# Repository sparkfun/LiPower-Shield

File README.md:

**NOTE:** *This product has been retired from our catalog. If you are looking for more up-to-date info, please check out some of these resources to see how other users are still hacking and improving on this product.*
* *[SparkFun Forum](https://forum.sparkfun.com/)*
* *[Comments Here on GitHub](https://github.com/sparkfun/LiPower-Shield/issues)*
* *[IRC Channel](https://www.sparkfun.com/news/263)*

SparkFun LiPower Shield
========================

[*SparkFun LiPower Shield (DEV-13158)*](https://www.sparkfun.com/products/13158)

This shield allows your Arduino to be powered from a 3.7V LiPo battery, while also charge and monitor the battery. 

Repository Contents
-------------------

* **/Hardware** - All Eagle design files (.brd, .sch)
* **/Production** - Production panel files (.brd)

Product Versions
----------------

* [DEV-13158](https://www.sparkfun.com/products/13158)- Version 1.1. Retired.
* [DEV-10711](https://www.sparkfun.com/products/retired/10711)- Version 1. Retired.

GitHub Version History
---------------
* [Version 1.1](https://github.com/sparkfun/LiPower-Shield/tree/V_1.1) - Latest hardware files. Retired..
* [Version 1](https://github.com/sparkfun/LiPower-Shield/tree/V_1) - Version 1. Retired. 

License Information
-------------------

This product is _**open source**_! 

Please review the LICENSE.md file for license information. 

If you have any questions or concerns on licensing, please contact techsupport@sparkfun.com.

Distributed as-is; no warranty is given.

- Your friends at SparkFun.

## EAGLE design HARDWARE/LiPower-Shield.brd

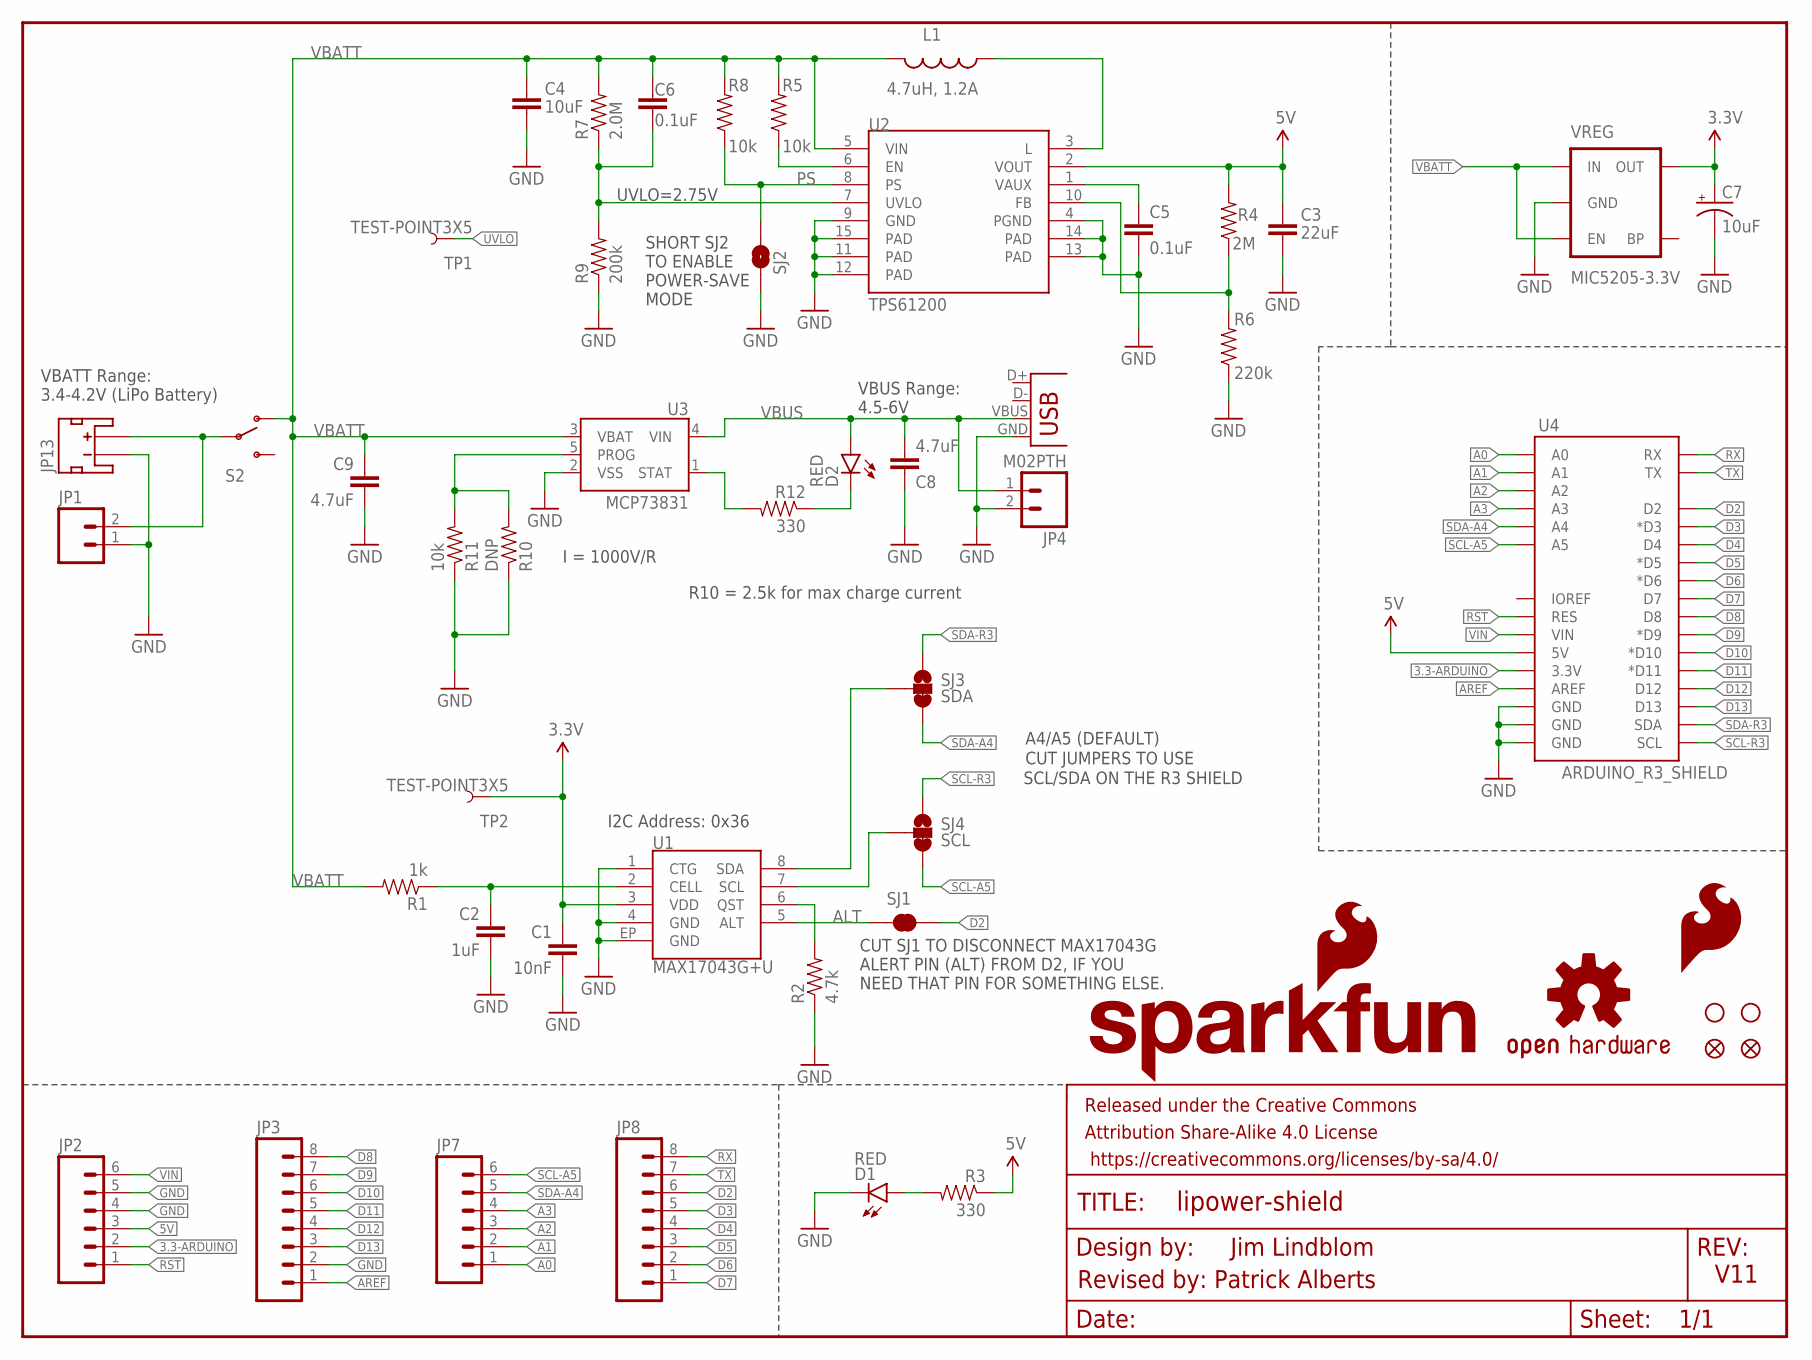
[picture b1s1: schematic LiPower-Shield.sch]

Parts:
C1: 10nF; 0603-CAP
C2: 1uF; 0603-CAP
C3: 22uF; 0805
C4: 10uF; 1206
C5, C6: 0.1uF; 0603-CAP
C7: 10uF; EIA3216
C8, C9: 4.7uF; 0603-CAP
D1, D2: RED; LED-0603
FID1, FID2: FIDUCIAL1X2; FIDUCIAL-1X2
FRAME1: FRAME-LETTER; CREATIVE_COMMONS
JP1: M021X02_NO_SILK; 1X02_NO_SILK
JP2, JP7: M06NO_SILK; 1X06_NO_SILK
JP3, JP8: M08NO_SILK; 1X08_NO_SILK
JP4: M02PTH; 1X02
JP9, JP10: STAND-OFFTIGHT; STAND-OFF-TIGHT
JP11: USBSMD; USB-MINIB
JP13: JST_2MM_MALE; JST-2-SMD
L1: 4.7uH, 1.2A; INDUCTOR_4.7UH
LOGO1: OSHW-LOGOS; OSHW-LOGO-S
LOGO2: SFE_LOGO_NAME_FLAME.2_INCH; SFE_LOGO_NAME_FLAME_.2
LOGO3: SFE_LOGO_FLAME.1_INCH; SFE_LOGO_FLAME_.1
R1: 1k; 0603-RES
R2: 4.7k; 0603-RES
R3, R12: 330; 0603-RES
R4: 2M; 0603-RES
R5, R8, R11: 10k; 0603-RES
R6: 220k; 0603-RES
R7: 2.0M; 0603-RES
R9: 200k; 0603-RES
R10: DNP; 1/6W-RES
S2: SWITCH-SPDT-SMD-A; SWITCH-SPST-SMD-A
SJ1: SOLDERJUMPERTRACE; SJ_2S-TRACE
SJ2: PS; SJ_2S-NO
SJ3: SDA; PAD-JUMPER-3-2OF3_NC_BY_TRACE_YES_SILK_FULL_BOX
SJ4: SCL; PAD-JUMPER-3-2OF3_NC_BY_TRACE_YES_SILK_FULL_BOX
TP1, TP2: TEST-POINT3X5; PAD.03X.05
U1: MAX17043G+U; TDFN-8
U2: TPS61200; QFN-10_PAD
U3: MCP73831; SOT23-5
U4: ARDUINO_R3_SHIELD; UNO_R3_SHIELD
VREG: MIC5205-3.3V; SOT23-5

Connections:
3.3-ARDUINO: JP2.2, U4.3.3V
3.3V: C1.1, C7.A (+), TP2.P$1, U1.3 (VDD), VREG.5 (OUT)
5V: C3.1, JP2.3, R3.1, R4.2, U2.2 (VOUT), U4.5V
A0: JP7.1, U4.A0
A1: JP7.2, U4.A1
A2: JP7.3, U4.A2
A3: JP7.4, U4.A3
ALT: SJ1.1, U1.5 (ALT)
AREF: JP3.1, U4.AREF
CELL: C2.1, R1.1, U1.2 (CELL)
D2: JP8.6, SJ1.2, U4.D2
D3: JP8.5, U4.D3 (*D3)
D4: JP8.4, U4.D4
D5: JP8.3, U4.D5 (*D5)
D6: JP8.2, U4.D6 (*D6)
D7: JP8.1, U4.D7
D8: JP3.8, U4.D8
D9: JP3.7, U4.D9 (*D9)
D10: JP3.6, U4.D10 (*D10)
D11: JP3.5, U4.D11 (*D11)
D12: JP3.4, U4.D12
D13: JP3.3, U4.D13
EN: R5.1, U2.6 (EN)
FB: R4.1, R6.2, U2.10 (FB)
GND: C1.2, C2.2, C3.2, C4.2, C5.2, C7.C (-), C8.1, C9.2, D1.C, JP1.1, JP2.4, JP2.5, JP3.2, JP4.2, JP11.GND, JP13.1 (-), R2.1, R6.1, R9.1, R10.1, R11.1, SJ2.1, U1.1 (CTG), U1.4 (GND), U1.EP (GND), U2.4 (PGND), U2.9 (GND), U2.11 (PAD), U2.12 (PAD), U2.13 (PAD), U2.14 (PAD), U2.15 (PAD), U3.2 (VSS), U4.GND@0 (GND), U4.GND@1 (GND), U4.GND@2 (GND), VREG.2 (GND)
unnamed: D1.A, R3.2
unnamed: L1.P$1 (1), U2.3 (L)
unnamed: C5.1, U2.1 (VAUX)
unnamed: D2.C, R12.1
unnamed: JP1.2, JP13.2 (+), S2.2
unnamed: SJ3.2, U1.8 (SDA)
PROG: R10.2, R11.2, U3.5 (PROG)
PS: R8.1, SJ2.2, U2.8 (PS)
QST: R2.2, U1.6 (QST)
RST: JP2.1, U4.RES
RX: JP8.8, U4.RX
SCL: SJ4.2, U1.7 (SCL)
SCL-A5: JP7.6, SJ4.3, U4.A5
SCL-R3: SJ4.1, U4.SCL
SDA-A4: JP7.5, SJ3.3, U4.A4
SDA-R3: SJ3.1, U4.SDA
STAT: R12.2, U3.1 (STAT)
TX: JP8.7, U4.TX
UVLO: C6.2, R7.1, R9.2, TP1.P$1, U2.7 (UVLO)
VBATT: C4.1, C6.1, C9.1, L1.P$2 (2), R1.2, R5.2, R7.2, R8.2, S2.1 (O), U2.5 (VIN), U3.3 (VBAT), VREG.1 (IN), VREG.3 (EN)
VBUS: C8.2, D2.A, JP4.1, JP11.VBUS, U3.4 (VIN)
VIN: JP2.6, U4.VIN

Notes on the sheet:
I = 1000V/R
R10 = 2.5k for max charge current
UVLO=2.75V
V11
Jim Lindblom
Revised by: Patrick Alberts
A4/A5 (DEFAULT)
CUT JUMPERS TO USE
SCL/SDA ON THE R3 SHIELD
SHORT SJ2 TO ENABLE POWER-SAVE MODE
CUT SJ1 TO DISCONNECT MAX17043G ALERT PIN (ALT) FROM D2, IF YOU NEED THAT PIN FOR SOMETHING ELSE.
I2C Address: 0x36
VBATT Range: 3.4-4.2V (LiPo Battery)
VBUS Range: 4.5-6V

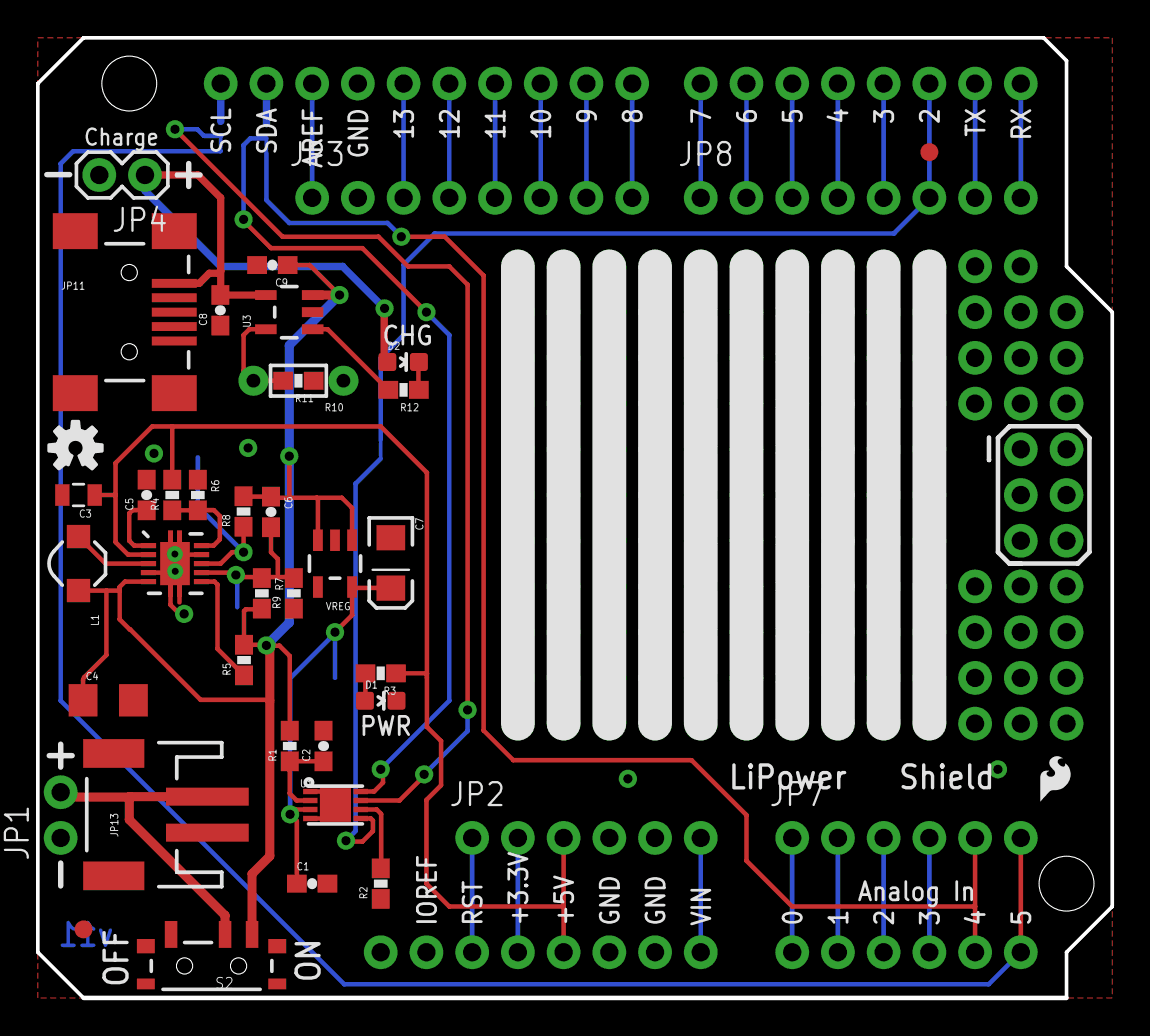
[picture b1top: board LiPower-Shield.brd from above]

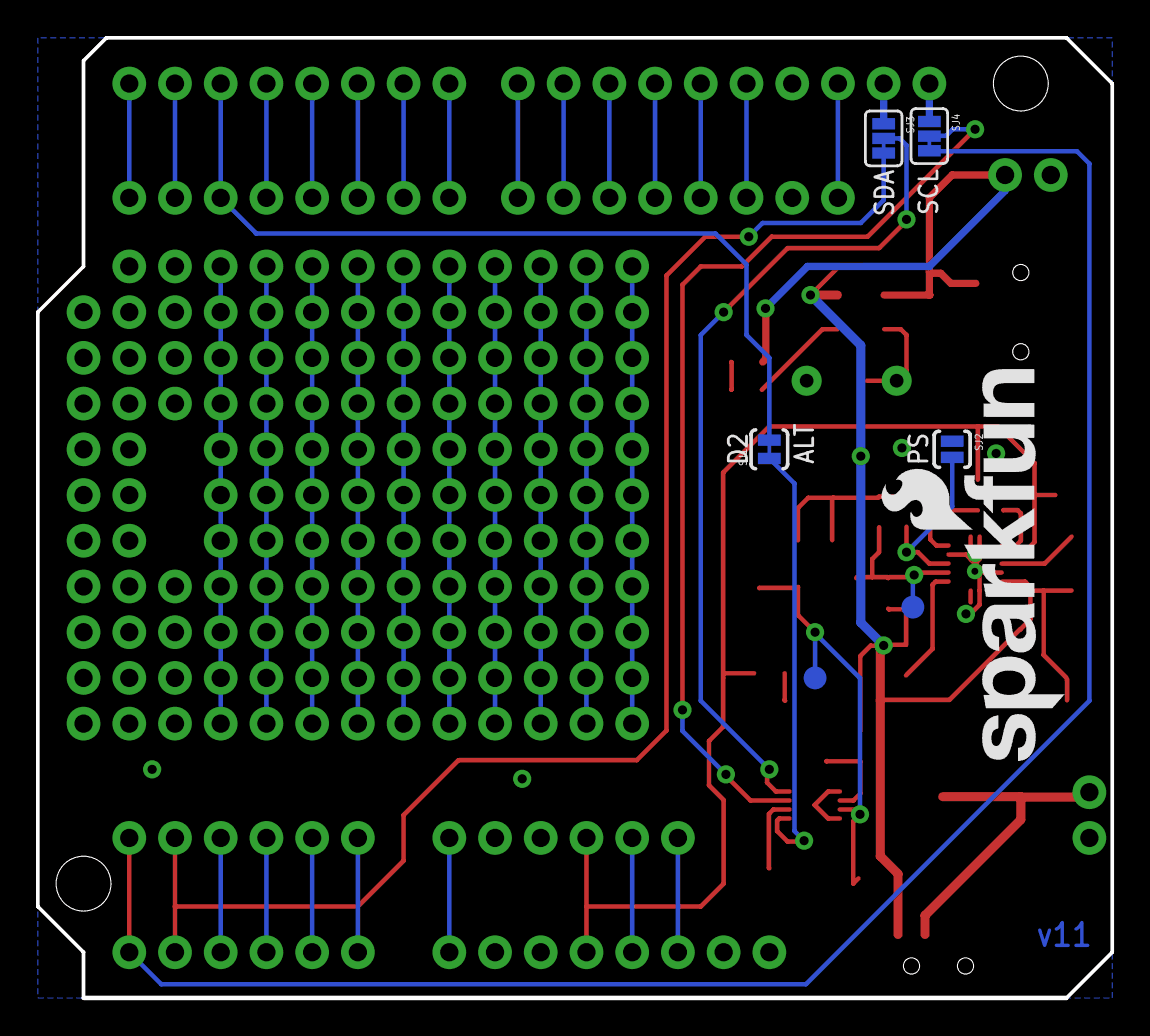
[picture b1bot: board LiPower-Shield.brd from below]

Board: 2 copper layers, 59.6 x 53.3 mm, 52 parts (7 on the bottom side), 47 nets.

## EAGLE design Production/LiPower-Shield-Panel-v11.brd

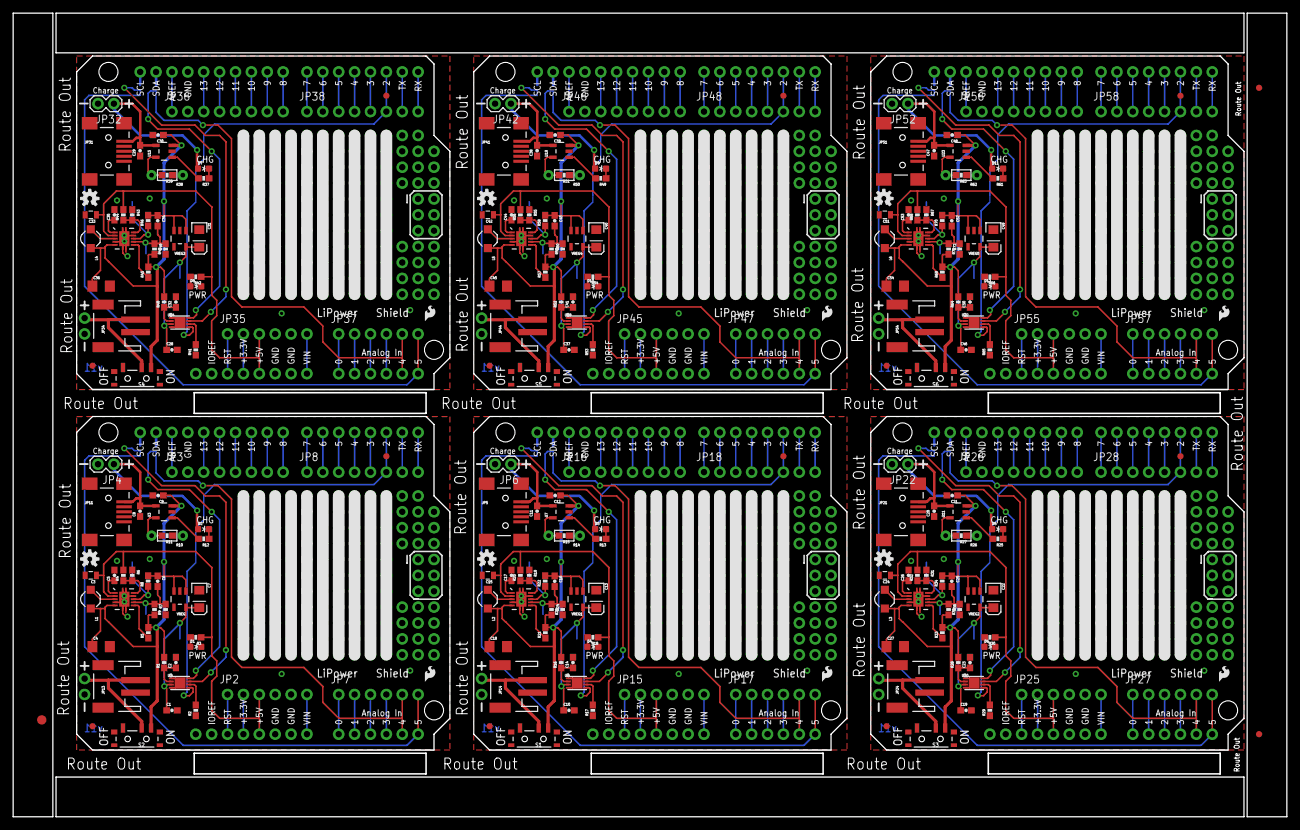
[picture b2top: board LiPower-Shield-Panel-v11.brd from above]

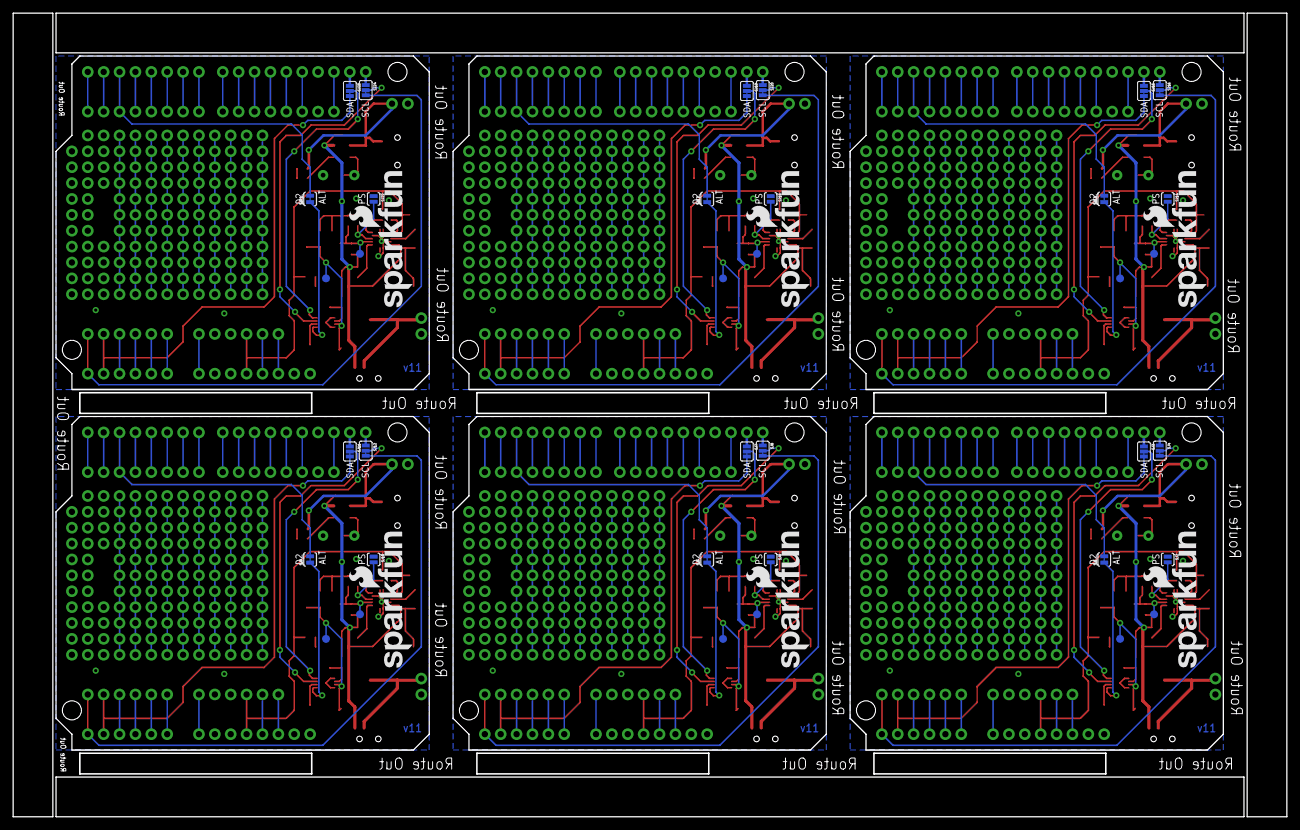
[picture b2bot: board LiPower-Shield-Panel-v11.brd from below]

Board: 2 copper layers, 203.7 x 128.5 mm, 309 parts (42 on the bottom side), 282 nets.

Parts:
C1, C10, C19, C28, C37, C46: 10nF; 0603-CAP
C2, C14, C23, C32, C41, C50: 1uF; 0603-CAP
C3, C15, C24, C33, C42, C51: 22uF; 0805
C4, C18, C27, C36, C45, C54: 10uF; 1206
C5, C6, C16, C17, C25, C26, C34, C35, C43, C44, C52, C53: 0.1uF; 0603-CAP
C7, C13, C22, C31, C40, C49: 10uF; EIA3216
C8, C9, C11, C12, C20, C21, C29, C30, C38, C39, C47, C48: 4.7uF; 0603-CAP
D1, D2, D3, D4, D5, D6, D7, D8, D9, D10, D11, D12: RED; LED-0603
E$1: FIDUCIAL-1.5X3
E$6, E$7: FIDUCIAL-1X2
FID1, FID2, FID3, FID4, FID5, FID6, FID7, FID8, FID9, FID10, FID11, FID12: FIDUCIAL1X2; FIDUCIAL-1X2
JP1, JP12, JP23, JP33, JP43, JP53: 1X02_NO_SILK
JP2, JP7, JP15, JP17, JP25, JP27, JP35, JP37, JP45, JP47, JP55, JP57: 1X06_NO_SILK
JP3, JP8, JP16, JP18, JP26, JP28, JP36, JP38, JP46, JP48, JP56, JP58: 1X08_NO_SILK
JP4, JP6, JP22, JP32, JP42, JP52: M02PTH; 1X02
JP5, JP11, JP21, JP31, JP41, JP51: USBSMD; USB-MINIB
JP9, JP10, JP19, JP20, JP29, JP30, JP39, JP40, JP49, JP50, JP59, JP60: STAND-OFFTIGHT; STAND-OFF-TIGHT
JP13, JP14, JP24, JP34, JP44, JP54: JST-2-SMD
L1, L2, L3, L4, L5, L6: 4.7uH, 1.2A; INDUCTOR_4.7UH
LOGO1, LOGO4, LOGO7, LOGO10, LOGO13, LOGO16: OSHW-LOGOS; OSHW-LOGO-S
LOGO2, LOGO5, LOGO8, LOGO11, LOGO14, LOGO17: SFE_LOGO_NAME_FLAME.2_INCH; SFE_LOGO_NAME_FLAME_.2
LOGO3, LOGO6, LOGO9, LOGO12, LOGO15, LOGO18: SFE_LOGO_FLAME.1_INCH; SFE_LOGO_FLAME_.1
R1, R16, R28, R40, R52, R64: 1k; 0603-RES
R2, R17, R29, R41, R53, R65: 4.7k; 0603-RES
R3, R12, R13, R18, R25, R30, R37, R42, R49, R54, R61, R66: 330; 0603-RES
R4, R20, R32, R44, R56, R68: 2M; 0603-RES
R5, R8, R11, R15, R21, R22, R27, R33, R34, R39, R45, R46, R51, R57, R58, R63, R69, R70: 10k; 0603-RES
R6, R19, R31, R43, R55, R67: 220k; 0603-RES
R7, R24, R36, R48, R60, R72: 2.0M; 0603-RES
R9, R23, R35, R47, R59, R71: 200k; 0603-RES
R10, R14, R26, R38, R50, R62: DNP; 1/6W-RES
S1, S2, S3, S4, S5, S6: SWITCH-SPST-SMD-A
SJ1, SJ5, SJ9, SJ13, SJ17, SJ21: SOLDERJUMPERTRACE; SJ_2S-TRACE
SJ2, SJ6, SJ10, SJ14, SJ18, SJ22: PS; SJ_2S-NO
SJ3, SJ7, SJ11, SJ15, SJ19, SJ23: SDA; PAD-JUMPER-3-2OF3_NC_BY_TRACE_YES_SILK_FULL_BOX
SJ4, SJ8, SJ12, SJ16, SJ20, SJ24: SCL; PAD-JUMPER-3-2OF3_NC_BY_TRACE_YES_SILK_FULL_BOX
TP1, TP2, TP3, TP4, TP5, TP6, TP7, TP8, TP9, TP10, TP11, TP12: TEST-POINT3X5; PAD.03X.05
U1, U6, U10, U14, U18, U22: MAX17043G+U; TDFN-8
U2, U8, U12, U16, U20, U24: TPS61200; QFN-10_PAD
U3, U7, U11, U15, U19, U23: MCP73831; SOT23-5
U4, U5, U9, U13, U17, U21: ARDUINO_R3_SHIELD; UNO_R3_SHIELD
VREG, VREG1, VREG2, VREG3, VREG4, VREG5: MIC5205-3.3V; SOT23-5

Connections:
3.3-ARDUINO: JP2.2, U4.3.3V
3.3-ARDUINO1: JP15.2, U5.3.3V
3.3-ARDUINO2: JP25.2, U9.3.3V
3.3-ARDUINO3: JP35.2, U13.3.3V
3.3-ARDUINO4: JP45.2, U17.3.3V
3.3-ARDUINO5: JP55.2, U21.3.3V
3.3V: C1.1, C7.A, TP2.P$1, U1.3, VREG.5
3.3V1: C10.1, C13.A, TP4.P$1, U6.3, VREG1.5
3.3V2: C19.1, C22.A, TP6.P$1, U10.3, VREG2.5
3.3V3: C28.1, C31.A, TP8.P$1, U14.3, VREG3.5
3.3V4: C37.1, C40.A, TP10.P$1, U18.3, VREG4.5
3.3V5: C46.1, C49.A, TP12.P$1, U22.3, VREG5.5
5V: C3.1, JP2.3, R3.1, R4.2, U2.2, U4.5V
5V1: C15.1, JP15.3, R18.1, R20.2, U5.5V, U8.2
5V2: C24.1, JP25.3, R30.1, R32.2, U9.5V, U12.2
5V3: C33.1, JP35.3, R42.1, R44.2, U13.5V, U16.2
5V4: C42.1, JP45.3, R54.1, R56.2, U17.5V, U20.2
5V5: C51.1, JP55.3, R66.1, R68.2, U21.5V, U24.2
A0: JP7.1, U4.A0
A1: JP7.2, U4.A1
A2: JP7.3, U4.A2
A3: JP7.4, U4.A3
A4: JP17.4, U5.A3
A5: JP17.3, U5.A2
A6: JP17.2, U5.A1
A7: JP17.1, U5.A0
A8: JP27.4, U9.A3
A9: JP27.3, U9.A2
A10: JP27.2, U9.A1
A11: JP27.1, U9.A0
A12: JP37.4, U13.A3
A13: JP37.3, U13.A2
A14: JP37.2, U13.A1
A15: JP37.1, U13.A0
A16: JP47.4, U17.A3
A17: JP47.3, U17.A2
A18: JP47.2, U17.A1
A19: JP47.1, U17.A0
A20: JP57.4, U21.A3
A21: JP57.3, U21.A2
A22: JP57.2, U21.A1
A23: JP57.1, U21.A0
ALT: SJ1.1, U1.5
ALT1: SJ5.1, U6.5
ALT2: SJ9.1, U10.5
ALT3: SJ13.1, U14.5
ALT4: SJ17.1, U18.5
ALT5: SJ21.1, U22.5
AREF: JP3.1, U4.AREF
AREF1: JP16.1, U5.AREF
AREF2: JP26.1, U9.AREF
AREF3: JP36.1, U13.AREF
AREF4: JP46.1, U17.AREF
AREF5: JP56.1, U21.AREF
CELL: C2.1, R1.1, U1.2
CELL1: C14.1, R16.1, U6.2
CELL2: C23.1, R28.1, U10.2
CELL3: C32.1, R40.1, U14.2
CELL4: C41.1, R52.1, U18.2
CELL5: C50.1, R64.1, U22.2
D1: JP18.5, U5.D3
D2: JP8.6, SJ1.2, U4.D2
D3: JP8.5, U4.D3
D4: JP8.4, U4.D4
D5: JP8.3, U4.D5
D6: JP8.2, U4.D6
D7: JP8.1, U4.D7
D8: JP3.8, U4.D8
D9: JP3.7, U4.D9
D10: JP3.6, U4.D10
D11: JP3.5, U4.D11
D12: JP3.4, U4.D12
D13: JP3.3, U4.D13
D14: JP18.4, U5.D4
D15: JP18.3, U5.D5
D16: JP18.1, U5.D7
D17: JP18.2, U5.D6
D18: JP16.8, U5.D8
D19: JP16.7, U5.D9
D20: JP16.6, U5.D10
D21: JP16.5, U5.D11
D22: JP16.4, U5.D12
D23: JP16.3, U5.D13
D24: JP18.6, SJ5.2, U5.D2
D25: JP28.5, U9.D3
D26: JP28.4, U9.D4
D27: JP28.3, U9.D5
D28: JP28.1, U9.D7
D29: JP28.2, U9.D6
D30: JP26.8, U9.D8
D31: JP26.7, U9.D9
D32: JP26.6, U9.D10
D33: JP26.5, U9.D11
D34: JP26.4, U9.D12
D35: JP26.3, U9.D13
D36: JP28.6, SJ9.2, U9.D2
D37: JP38.5, U13.D3
D38: JP38.4, U13.D4
D39: JP38.3, U13.D5
D40: JP38.1, U13.D7
D41: JP38.2, U13.D6
D42: JP36.8, U13.D8
D43: JP36.7, U13.D9
D44: JP36.6, U13.D10
D45: JP36.5, U13.D11
D46: JP36.4, U13.D12
D47: JP36.3, U13.D13
D48: JP38.6, SJ13.2, U13.D2
D49: JP48.5, U17.D3
D50: JP48.4, U17.D4
D51: JP48.3, U17.D5
D52: JP48.1, U17.D7
D53: JP48.2, U17.D6
D54: JP46.8, U17.D8
D55: JP46.7, U17.D9
D56: JP46.6, U17.D10
D57: JP46.5, U17.D11
D58: JP46.4, U17.D12
D59: JP46.3, U17.D13
D60: JP48.6, SJ17.2, U17.D2
D61: JP58.5, U21.D3
D62: JP58.4, U21.D4
D63: JP58.3, U21.D5
D64: JP58.1, U21.D7
D65: JP58.2, U21.D6
D66: JP56.8, U21.D8
D67: JP56.7, U21.D9
D68: JP56.6, U21.D10
D69: JP56.5, U21.D11
D70: JP56.4, U21.D12
D71: JP56.3, U21.D13
D72: JP58.6, SJ21.2, U21.D2
EN: R5.1, U2.6
EN1: R21.1, U8.6
EN2: R33.1, U12.6
EN3: R45.1, U16.6
EN4: R57.1, U20.6
EN5: R69.1, U24.6
FB: R4.1, R6.2, U2.10
FB1: R19.2, R20.1, U8.10
FB2: R31.2, R32.1, U12.10
FB3: R43.2, R44.1, U16.10
FB4: R55.2, R56.1, U20.10
FB5: R67.2, R68.1, U24.10
GND: C1.2, C2.2, C3.2, C4.2, C5.2, C7.C, C8.1, C9.2, D1.C, JP1.1, JP2.4, JP2.5, JP3.2, JP4.2, JP11.GND, JP13.1, R2.1, R6.1, R9.1, R10.1, R11.1, SJ2.1, U1.1, U1.4, U1.EP, U2.4, U2.9, U2.11, U2.12, U2.13, U2.14, U2.15, U3.2, U4.GND@0, U4.GND@1, U4.GND@2, VREG.2
GND1: C10.2, C11.1, C12.2, C13.C, C14.2, C15.2, C17.2, C18.2, D4.C, JP5.GND, JP6.2, JP12.1, JP14.1, JP15.4, JP15.5, JP16.2, R14.1, R15.1, R17.1, R19.1, R23.1, SJ6.1, U5.GND@0, U5.GND@1, U5.GND@2, U6.1, U6.4, U6.EP, U7.2, U8.4, U8.9, U8.11, U8.12, U8.13, U8.14, U8.15, VREG1.2
GND2: C19.2, C20.1, C21.2, C22.C, C23.2, C24.2, C26.2, C27.2, D6.C, JP21.GND, JP22.2, JP23.1, JP24.1, JP25.4, JP25.5, JP26.2, R26.1, R27.1, R29.1, R31.1, R35.1, SJ10.1, U9.GND@0, U9.GND@1, U9.GND@2, U10.1, U10.4, U10.EP, U11.2, U12.4, U12.9, U12.11, U12.12, U12.13, U12.14, U12.15, VREG2.2
GND3: C28.2, C29.1, C30.2, C31.C, C32.2, C33.2, C35.2, C36.2, D8.C, JP31.GND, JP32.2, JP33.1, JP34.1, JP35.4, JP35.5, JP36.2, R38.1, R39.1, R41.1, R43.1, R47.1, SJ14.1, U13.GND@0, U13.GND@1, U13.GND@2, U14.1, U14.4, U14.EP, U15.2, U16.4, U16.9, U16.11, U16.12, U16.13, U16.14, U16.15, VREG3.2
GND4: C37.2, C38.1, C39.2, C40.C, C41.2, C42.2, C44.2, C45.2, D10.C, JP41.GND, JP42.2, JP43.1, JP44.1, JP45.4, JP45.5, JP46.2, R50.1, R51.1, R53.1, R55.1, R59.1, SJ18.1, U17.GND@0, U17.GND@1, U17.GND@2, U18.1, U18.4, U18.EP, U19.2, U20.4, U20.9, U20.11, U20.12, U20.13, U20.14, U20.15, VREG4.2
GND5: C46.2, C47.1, C48.2, C49.C, C50.2, C51.2, C53.2, C54.2, D12.C, JP51.GND, JP52.2, JP53.1, JP54.1, JP55.4, JP55.5, JP56.2, R62.1, R63.1, R65.1, R67.1, R71.1, SJ22.1, U21.GND@0, U21.GND@1, U21.GND@2, U22.1, U22.4, U22.EP, U23.2, U24.4, U24.9, U24.11, U24.12, U24.13, U24.14, U24.15, VREG5.2
unnamed: D1.A, R3.2
unnamed: L1.P$1, U2.3
unnamed: C5.1, U2.1
unnamed: D2.C, R12.1
unnamed: JP1.2, JP13.2, S2.2
unnamed: SJ3.2, U1.8
unnamed: D3.C, R13.1
unnamed: SJ7.2, U6.8
unnamed: D4.A, R18.2
unnamed: L2.P$1, U8.3
unnamed: C17.1, U8.1
unnamed: JP12.2, JP14.2, S1.2
unnamed: D5.C, R25.1
unnamed: SJ11.2, U10.8
unnamed: D6.A, R30.2
unnamed: L3.P$1, U12.3
unnamed: C26.1, U12.1
unnamed: JP23.2, JP24.2, S3.2
unnamed: D7.C, R37.1
unnamed: SJ15.2, U14.8
unnamed: D8.A, R42.2
unnamed: L4.P$1, U16.3
unnamed: C35.1, U16.1
unnamed: JP33.2, JP34.2, S4.2
unnamed: D9.C, R49.1
unnamed: SJ19.2, U18.8
unnamed: D10.A, R54.2
unnamed: L5.P$1, U20.3
unnamed: C44.1, U20.1
unnamed: JP43.2, JP44.2, S5.2
unnamed: D11.C, R61.1
unnamed: SJ23.2, U22.8
unnamed: D12.A, R66.2
unnamed: L6.P$1, U24.3
unnamed: C53.1, U24.1
unnamed: JP53.2, JP54.2, S6.2
PROG: R10.2, R11.2, U3.5
PROG1: R14.2, R15.2, U7.5
PROG2: R26.2, R27.2, U11.5
PROG3: R38.2, R39.2, U15.5
PROG4: R50.2, R51.2, U19.5
PROG5: R62.2, R63.2, U23.5
PS: R8.1, SJ2.2, U2.8
PS1: R22.1, SJ6.2, U8.8
PS2: R34.1, SJ10.2, U12.8
PS3: R46.1, SJ14.2, U16.8
PS4: R58.1, SJ18.2, U20.8
PS5: R70.1, SJ22.2, U24.8
QST: R2.2, U1.6
QST1: R17.2, U6.6
QST2: R29.2, U10.6
QST3: R41.2, U14.6
QST4: R53.2, U18.6
QST5: R65.2, U22.6
RST: JP2.1, U4.RES
RST1: JP15.1, U5.RES
RST2: JP25.1, U9.RES
RST3: JP35.1, U13.RES
RST4: JP45.1, U17.RES
RST5: JP55.1, U21.RES
RX: JP8.8, U4.RX
RX1: JP18.8, U5.RX
RX2: JP28.8, U9.RX
RX3: JP38.8, U13.RX
RX4: JP48.8, U17.RX
RX5: JP58.8, U21.RX
SCL: SJ4.2, U1.7
SCL1: SJ8.2, U6.7
SCL2: SJ12.2, U10.7
SCL3: SJ16.2, U14.7
SCL4: SJ20.2, U18.7
SCL5: SJ24.2, U22.7
SCL-A1: JP17.6, SJ8.3, U5.A5
SCL-A2: JP27.6, SJ12.3, U9.A5
SCL-A3: JP37.6, SJ16.3, U13.A5
SCL-A4: JP47.6, SJ20.3, U17.A5
SCL-A5: JP7.6, SJ4.3, U4.A5
SCL-A6: JP57.6, SJ24.3, U21.A5
SCL-R1: SJ8.1, U5.SCL
SCL-R2: SJ12.1, U9.SCL
SCL-R3: SJ4.1, U4.SCL
SCL-R4: SJ16.1, U13.SCL
SCL-R5: SJ20.1, U17.SCL
SCL-R6: SJ24.1, U21.SCL
SDA-A1: JP17.5, SJ7.3, U5.A4
SDA-A2: JP27.5, SJ11.3, U9.A4
SDA-A3: JP37.5, SJ15.3, U13.A4
SDA-A4: JP7.5, SJ3.3, U4.A4
SDA-A5: JP47.5, SJ19.3, U17.A4
SDA-A6: JP57.5, SJ23.3, U21.A4
SDA-R1: SJ7.1, U5.SDA
SDA-R2: SJ11.1, U9.SDA
SDA-R3: SJ3.1, U4.SDA
SDA-R4: SJ15.1, U13.SDA
SDA-R5: SJ19.1, U17.SDA
SDA-R6: SJ23.1, U21.SDA
STAT: R12.2, U3.1
STAT1: R13.2, U7.1
STAT2: R25.2, U11.1
STAT3: R37.2, U15.1
STAT4: R49.2, U19.1
STAT5: R61.2, U23.1
TX: JP8.7, U4.TX
TX1: JP18.7, U5.TX
TX2: JP28.7, U9.TX
TX3: JP38.7, U13.TX
TX4: JP48.7, U17.TX
TX5: JP58.7, U21.TX
UVLO: C6.2, R7.1, R9.2, TP1.P$1, U2.7
UVLO1: C16.2, R23.2, R24.1, TP3.P$1, U8.7
UVLO2: C25.2, R35.2, R36.1, TP5.P$1, U12.7
UVLO3: C34.2, R47.2, R48.1, TP7.P$1, U16.7
UVLO4: C43.2, R59.2, R60.1, TP9.P$1, U20.7
UVLO5: C52.2, R71.2, R72.1, TP11.P$1, U24.7
VBATT: C4.1, C6.1, C9.1, L1.P$2, R1.2, R5.2, R7.2, R8.2, S2.1, U2.5, U3.3, VREG.1, VREG.3
VBATT1: C12.1, C16.1, C18.1, L2.P$2, R16.2, R21.2, R22.2, R24.2, S1.1, U7.3, U8.5, VREG1.1, VREG1.3
VBATT2: C21.1, C25.1, C27.1, L3.P$2, R28.2, R33.2, R34.2, R36.2, S3.1, U11.3, U12.5, VREG2.1, VREG2.3
VBATT3: C30.1, C34.1, C36.1, L4.P$2, R40.2, R45.2, R46.2, R48.2, S4.1, U15.3, U16.5, VREG3.1, VREG3.3
VBATT4: C39.1, C43.1, C45.1, L5.P$2, R52.2, R57.2, R58.2, R60.2, S5.1, U19.3, U20.5, VREG4.1, VREG4.3
VBATT5: C48.1, C52.1, C54.1, L6.P$2, R64.2, R69.2, R70.2, R72.2, S6.1, U23.3, U24.5, VREG5.1, VREG5.3
VBUS: C8.2, D2.A, JP4.1, JP11.VBUS, U3.4
VBUS1: C11.2, D3.A, JP5.VBUS, JP6.1, U7.4
VBUS2: C20.2, D5.A, JP21.VBUS, JP22.1, U11.4
VBUS3: C29.2, D7.A, JP31.VBUS, JP32.1, U15.4
VBUS4: C38.2, D9.A, JP41.VBUS, JP42.1, U19.4
VBUS5: C47.2, D11.A, JP51.VBUS, JP52.1, U23.4
VIN: JP2.6, U4.VIN
VIN1: JP15.6, U5.VIN
VIN2: JP25.6, U9.VIN
VIN3: JP35.6, U13.VIN
VIN4: JP45.6, U17.VIN
VIN5: JP55.6, U21.VIN

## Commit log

2013-09-11 Initial Commit
    -gitignore
    -brd
    -sch
2013-09-11 Had to re-commit original files
    The v13 files that I pulled from the network are not what we have on
    storefront. commited v12, also from the network, seems to be the same
    as the SF product.
2013-12-11 Updating README
2014-06-13 Computer Change
    0603 updated, r3 update. JST update, trace rework and schematic
    cleanup.
2014-06-26 re-up
    Re Committed the original files.
2014-08-18 Added OSHW, SPK Logo
    Also added flags to schematic
2014-08-18 Computer Change
2014-10-06 Added jumpers, isolated isp headers, trace reroutes
    Added SCL SDA jumpers
    Thermal relief for ground headers as well as changing all vias to
    headers.
    Added Test point for qc
2014-10-07 added dimension line, removed silk on proto headers
2014-11-12 Changed res values on the UVLO line.
2014-11-12 Changed UVLO voltage in SCH
2014-11-14 Moved Sparkfun silk
2014-11-18 Changed r7 back to 2m
2014-11-20 Added test point, Lines around Sch parts and Prod Att
2014-11-20 Added info on SDA/SCL jumpers
2014-11-20 Adding descriptions to SJ1 and SJ2.
2014-11-21 Reduced paste on IC's
2014-11-21 Adding MAX17043G I2C address to schematic.
2014-11-21 Adding voltage input range notes.
2014-11-21 Added prod id's for nduc/caps
2014-11-21 Updated paste on IC's
2014-11-21 Schematic Cleanup
    fixed all of these...
    1) GND and 5V symbols need to be rotated "up" and "down".
    2) all LEDs prefixes should be "D#"
    3) R4 needs to be shifted down one grid space. The resulting 4 way
    junction will need to be fixed then too.
    4) J1 should have a prefix of JP#
2014-11-24 changed fids to regular from micro
2014-12-09 Fixed current QC checklist issues.
2014-12-10 Moved net on LED
2015-01-12 created panel v11
2015-10-22 Updating README with new product info, adding License file
2015-10-22 Adding new picture to readme
2018-08-02 Updates
    -Update README.md
    -Update Hardware Directory for Eagle Files
2018-08-02 Hardware Folder Issues
    Weird GitHub display Issue with Hardware folder. Removing directory.
2018-08-02 New Hardware Folder
    Weird issue where it was displaying eagle files two separate folders: HARDWARE and Hardware.

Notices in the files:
parts and their libraries:
SparkFun-LED: Licensing: Creative Commons ShareAlike 4.0 International - https://creativecommons.org/licenses/by-sa/4.0
SparkFun-Aesthetics: Released under the Creative Commons Attribution Share-Alike 4.0 License
SparkFun-Aesthetics: https://creativecommons.org/licenses/by-sa/4.0
